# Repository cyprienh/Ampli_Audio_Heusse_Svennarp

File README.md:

# BE Électronique 3A IMACS

Bonjour ! Ceci est le repo du Bureau d'Étude Électronique de 3A IMACS 2022 à l'INSA Toulouse. Ce projet à été réalisé sur **KiCad**. Il permettra à terme de réaliser le PCB d'un amplificateur audio.

## Installation

Vous pouvez télécharger (directement sur GitHub ou via la commande git) le dossier et l'ouvrir sur **KiCad**. Ce projet à été réalisé sur la version *6.0.2* et sur *MacOS*.
>Vous pouvez télécharger **KiCad** à [ce lien](https://www.kicad.org/download/).

## Progression

- Le schéma électrique à été réalisé, il ne reste plus qu'à renseigner les valeurs des résistances et de certains condensateurs.
- L'association entre les symboles et les empreintes est quasiment complète.
- Les symboles et empreintes nécessaires ont été importé(e)s.

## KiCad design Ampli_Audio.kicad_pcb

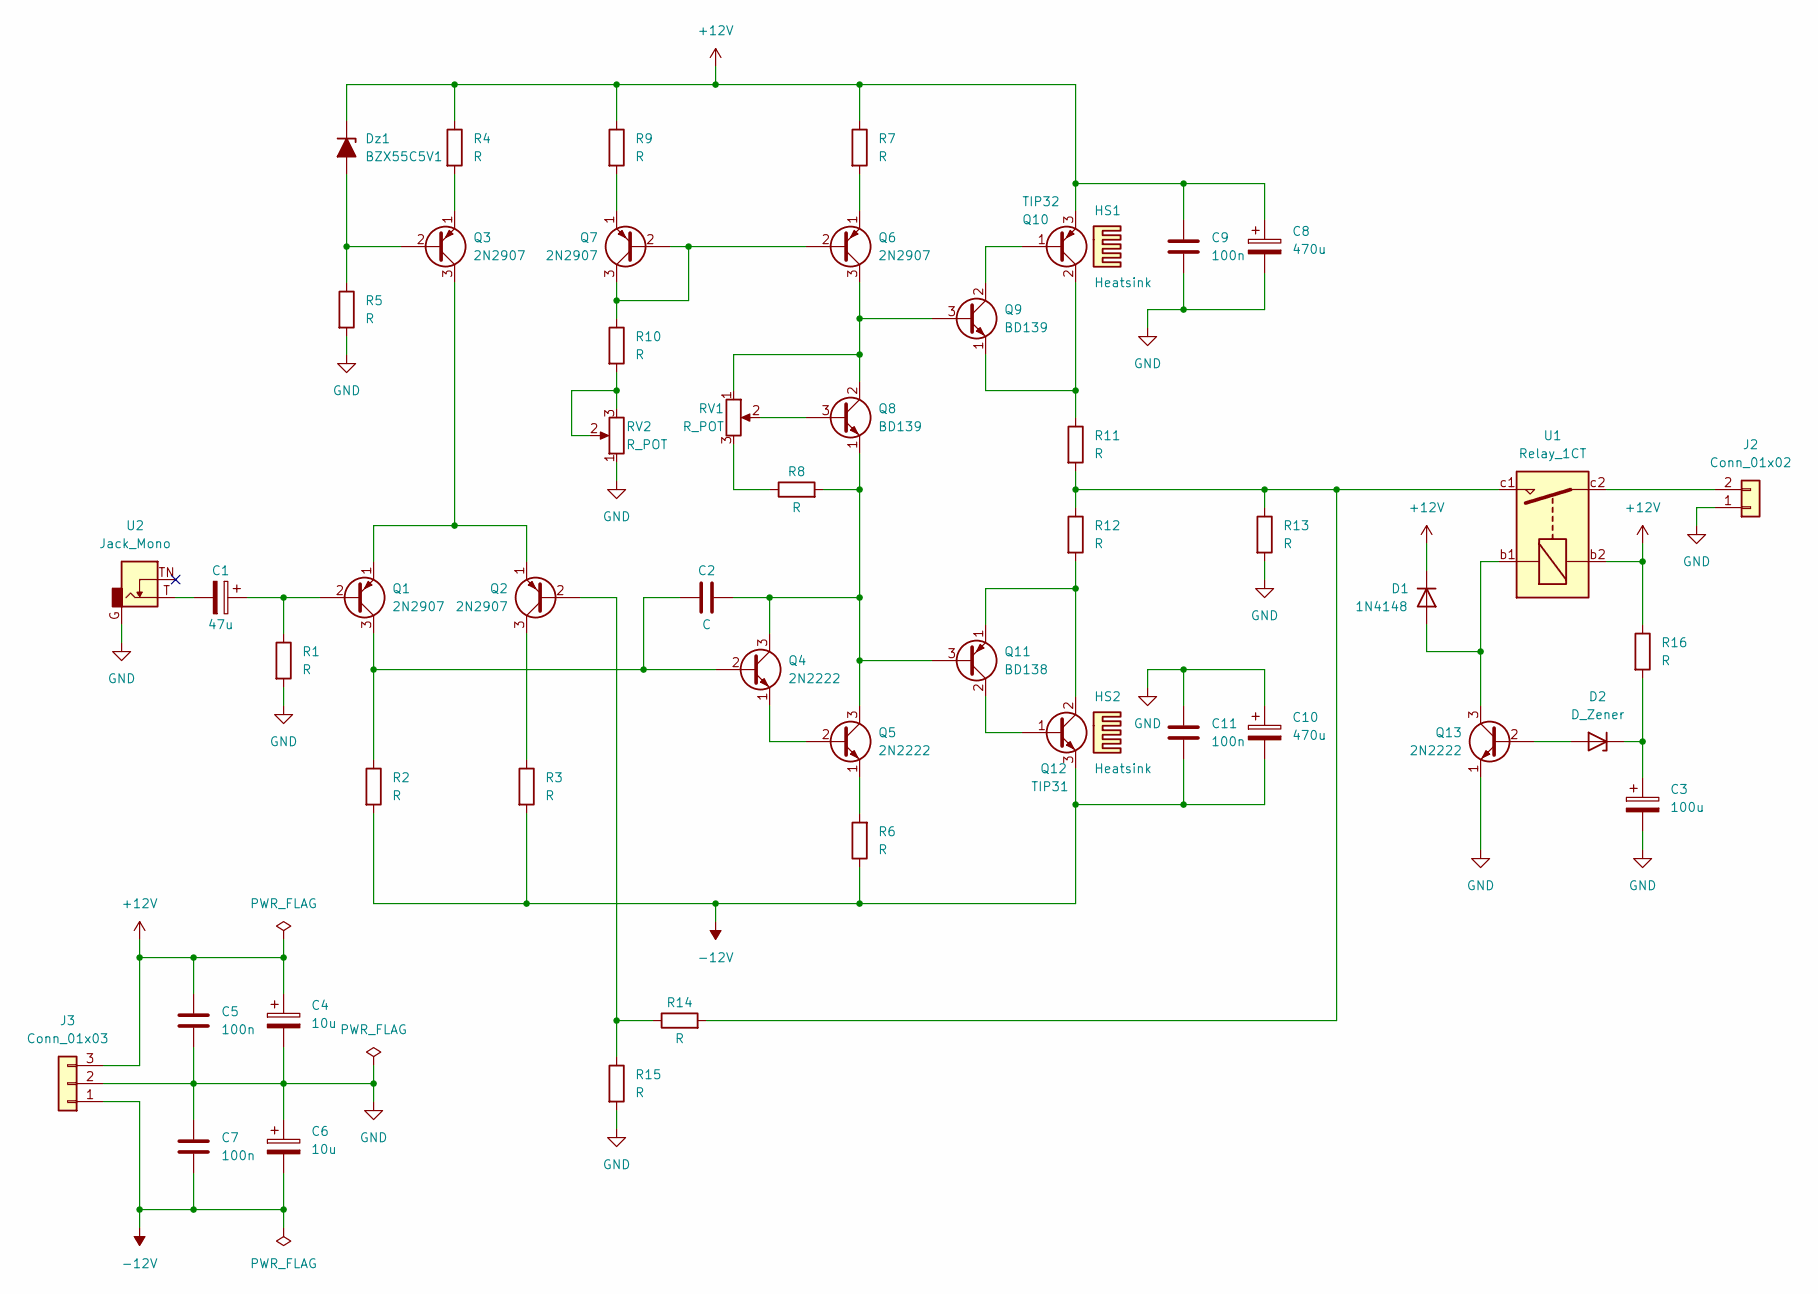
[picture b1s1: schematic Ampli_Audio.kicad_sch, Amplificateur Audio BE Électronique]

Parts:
C1: 47u; CP_Radial_D8.0mm_P5.00mm
C2: C; C_Rect_L7.2mm_W3.5mm_P5.00mm_FKS2_FKP2_MKS2_MKP2
C3: 100u; CP_Radial_D8.0mm_P5.00mm
C4, C6: 10u; CP_Radial_D8.0mm_P5.00mm
C5, C7, C9, C11: 100n; C_Rect_L7.2mm_W3.5mm_P5.00mm_FKS2_FKP2_MKS2_MKP2
C8, C10: 470u; CP_Radial_D12.5mm_P5.00mm
D1: 1N4148; D_DO-35_SOD27_P10.16mm_Horizontal
D2: D_Zener; D_DO-35_SOD27_P10.16mm_Horizontal
Dz1: BZX55C5V1; D_DO-35_SOD27_P10.16mm_Horizontal
HS1, HS2: Heatsink; Heatsink_Fischer_SK104-STC-STIC_35x13mm_2xDrill2.5mm
J2: Conn_01x02; PhoenixContact_MSTBVA_2,5_2-G-5,08_1x02_P5.08mm_Vertical
J3: Conn_01x03; PhoenixContact_MSTBVA_2,5_3-G-5,08_1x03_P5.08mm_Vertical
Q1, Q2, Q3, Q6, Q7: 2N2907; TO-18-3
Q4, Q5, Q13: 2N2222; TO-18-3
Q8, Q9: BD139; TO-126-3_Vertical
Q10: TIP32; TO-220-3_Vertical
Q11: BD138; TO-126-3_Vertical
Q12: TIP31; TO-220-3_Vertical
R1, R2, R3, R4, R5, R6, R7, R8, R9, R10, R13, R14, R15, R16: R; R_Axial_DIN0207_L6.3mm_D2.5mm_P10.16mm_Horizontal
R11, R12: R; R_Axial_DIN0516_L15.5mm_D5.0mm_P20.32mm_Horizontal
RV1, RV2: R_POT; Potentiometer_Bourns_3296W_Vertical
U1: Relay_1CT; Relais_112LMH2
U2: Jack_Mono; Jack_35RAPC2AV

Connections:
+12V: C4.1, C5.1, C8.1, C9.1, D1.1 (K), Dz1.1 (K), J3.3, Q10.3 (E), R4.1, R7.1, R9.1, R16.1, U1.b2
-12V: C6.2, C7.2, C10.2, C11.2, J3.1, Q12.3 (E), R2.2, R3.2, R6.1
GND: C3.2, C4.2, C5.2, C6.1, C7.1, C8.2, C9.2, C10.1, C11.1, J2.1, J3.2, Q13.1 (E), R1.2, R5.2, R13.2, R15.2, RV2.1, U2.G
unnamed: C1.1, Q1.2 (B), R1.1
unnamed: C1.2, U2.T
unnamed: C2.1, Q1.3 (C), Q4.2 (B), R2.1
unnamed: C2.2, Q4.3 (C), Q5.3 (C), Q8.1 (E), Q11.3 (B), R8.2
unnamed: C3.1, D2.1 (K), R16.2
unnamed: D1.2 (A), Q13.3 (C), U1.b1
unnamed: D2.2 (A), Q13.2 (B)
unnamed: Dz1.2 (A), Q3.2 (B), R5.1
unnamed: J2.2, U1.c2
unnamed: Q1.1 (E), Q2.1 (E), Q3.3 (C)
unnamed: Q2.2 (B), R14.1, R15.1
unnamed: Q2.3 (C), R3.1
unnamed: Q3.1 (E), R4.2
unnamed: Q4.1 (E), Q5.2 (B)
unnamed: Q5.1 (E), R6.2
unnamed: Q6.1 (E), R7.2
unnamed: Q6.2 (B), Q7.2 (B), Q7.3 (C), R10.1
unnamed: Q6.3 (C), Q8.2 (C), Q9.3 (B), RV1.1
unnamed: Q7.1 (E), R9.2
unnamed: Q8.3 (B), RV1.2
unnamed: Q9.2 (C), Q10.1 (B)
unnamed: Q9.1 (E), Q10.2 (C), R11.1
unnamed: Q11.1 (E), Q12.2 (C), R12.2
unnamed: Q11.2 (C), Q12.1 (B)
unnamed: R8.1, RV1.3
unnamed: R10.2, RV2.2, RV2.3
unnamed: R11.2, R12.1, R13.1, R14.2, U1.c1

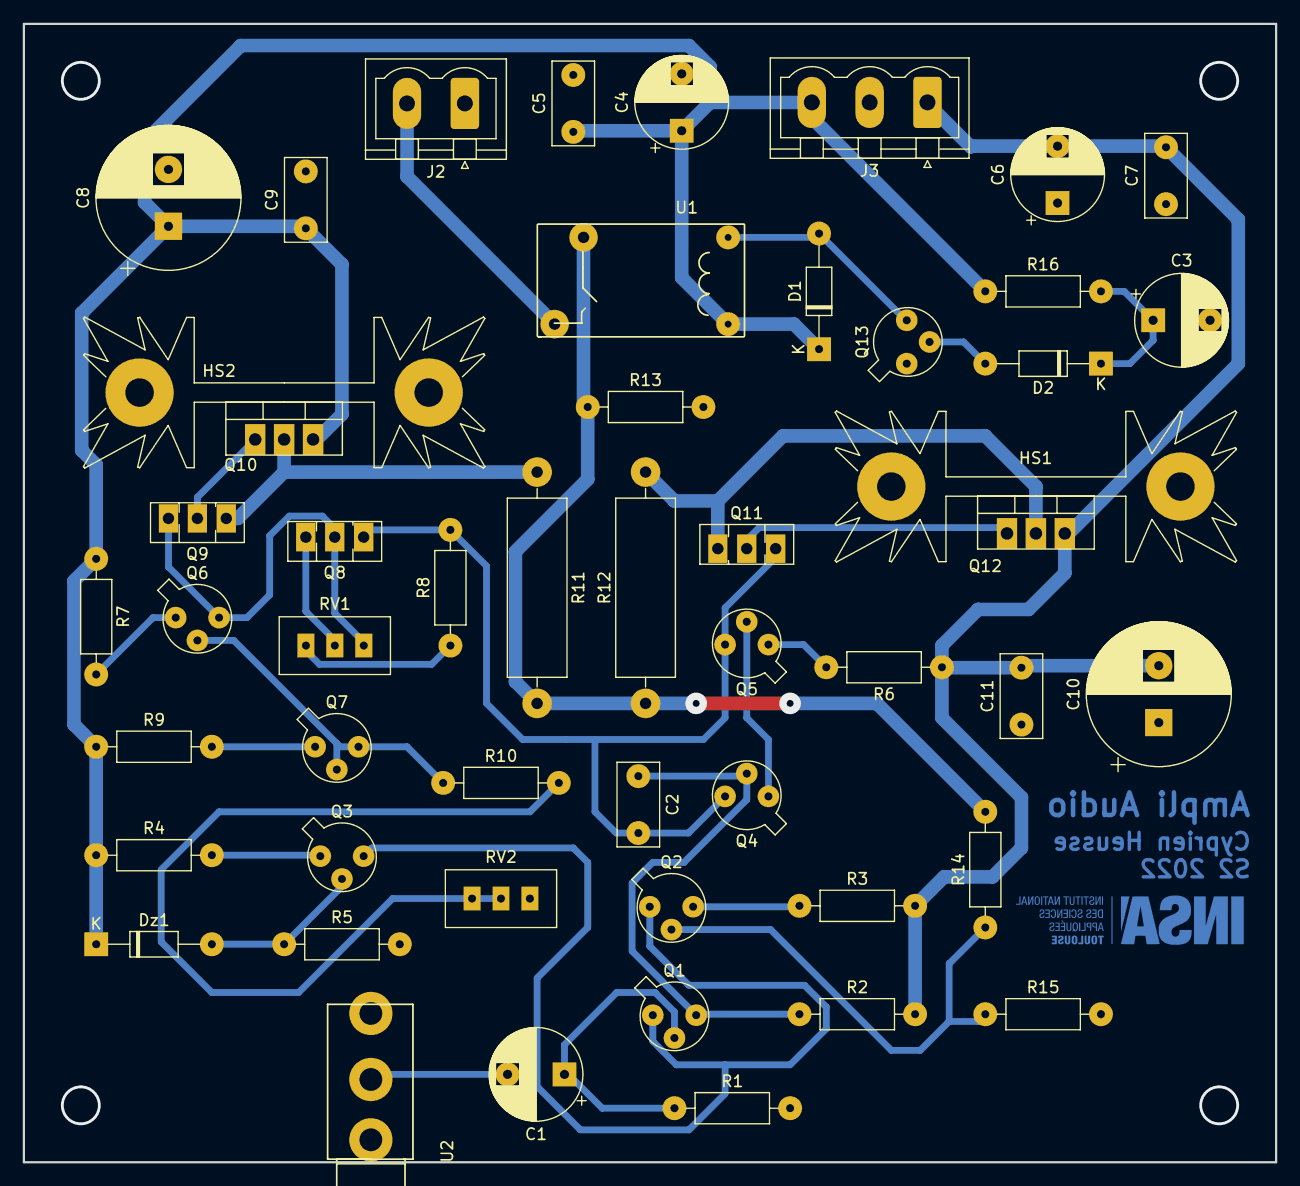
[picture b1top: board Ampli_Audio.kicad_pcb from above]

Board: 2 copper layers, 110.0 x 100.0 mm, 51 parts (0 on the bottom side), 30 nets.

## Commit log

2022-03-08 Création du repo et schématique
2022-03-08 Mise à jour de README.md
2022-03-08 Supression des fichiers inutiles
2022-03-11 Placement composants sur PCB
2022-03-13 Correction & Routage
2022-03-13 Révisions PCB
2022-03-15 Modification texte
